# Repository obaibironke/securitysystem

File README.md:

# securitysystem
A custom motion sensor triggered security system that alerts me whenever someone enters my room. I made it because my sister kept entering myroom without me knowing so now I can catch her. It detects motion using a PIR sensor that will be soldered onto the PCB directly. It then send this information to the ESP32-S3 so that it can be logged onto the Google Sheet as well as be sent as a Telegram message. The MAX7219 display is just to show how many times motion has been detected since the system was last armed.

Hardware:

Custom PCB
XIAO ESP32-S3
PIR motion sensor
Photoresistor
MAX7219 8-digit display
Active buzzer
Arm/disarm button
Power switch
Custom enclosure

Features:

WiFi connectivity with auto-reconnect
Telegram bot alerts for motion, arm/disarm, system online
Telegram bot commands
Google Sheets event logging
Night mode that auto-disarms in daylight using photoresistor
Force disarm via Telegram
High motion alert that triggers when 3+ detections in a window
Motion counter displayed on 8-digit display, capped at 99999999
Different buzzer patterns for armed, disarmed, and motion detected
Motion timeout to prevent spam detection

BOM:

Images:

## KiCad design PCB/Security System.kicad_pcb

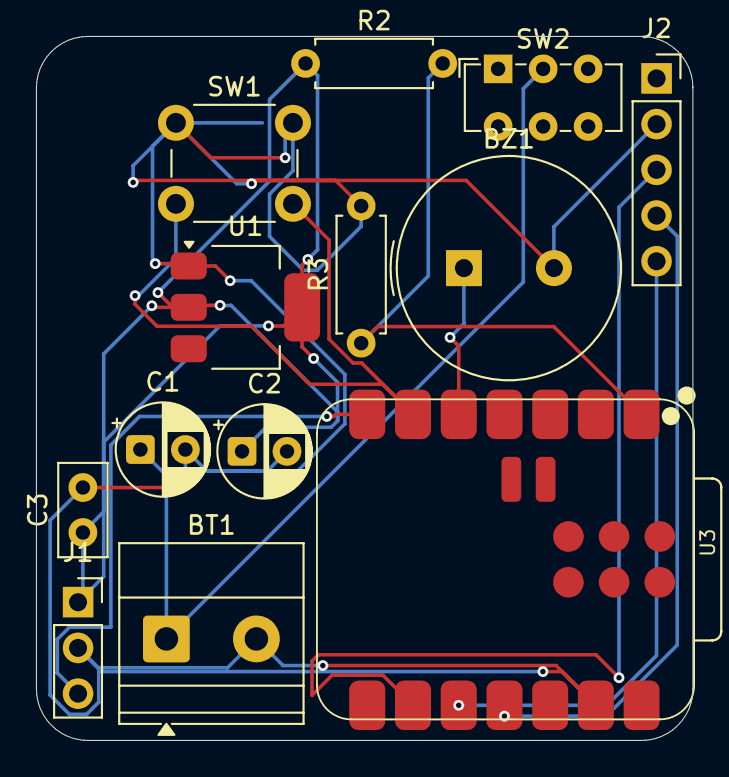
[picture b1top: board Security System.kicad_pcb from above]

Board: 2 copper layers, 36.5 x 39.1 mm, 13 parts (0 on the bottom side), 10 nets.

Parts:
BT1: Battery_Cell; TerminalBlock_Phoenix_MKDS-1,5-2_1x02_P5.00mm_Horizontal
BZ1: Buzzer; Buzzer_TDK_PS1240P02BT_D12.2mm_H6.5mm
C1, C2: C_Polarized; CP_Radial_D5.0mm_P2.50mm
C3: C; C_Disc_D5.0mm_W2.5mm_P2.50mm
J1: Conn_01x03; PinSocket_1x03_P2.54mm_Vertical
J2: Conn_01x05_Pin; PinSocket_1x05_P2.54mm_Vertical
R2: R_Photo; R_Axial_DIN0207_L6.3mm_D2.5mm_P7.62mm_Horizontal
R3: R; R_Axial_DIN0207_L6.3mm_D2.5mm_P7.62mm_Horizontal
SW1: SW_Push; SW_PUSH_6mm
SW2: SW_SPDT; SW_E-Switch_EG1271_SPDT
U1: AMS1117-3.3; SOT-223-3_TabPin2
U3: Val**; XIAO-ESP32-C3-SMD

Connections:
+3.3V: C2.1, C3.1, J1.1, R2.1, U1.2 (VO)
+BATT: BT1.1 (+), C1.1, SW2.2 (B)
GND: BT1.2 (-), BZ1.2 (-), C1.2, C2.2, C3.2, J1.2, J2.2, R3.2, SW1.1, U1.1 (GND), U3.13 (GND)
unnamed: BZ1.1 (+), U3.5 (GPIO6_D4_SDA)
unnamed: J1.3, U3.7 (GPIO21_D6_TX)
unnamed: J2.3, U3.9 (GPIO8_D8_SCK)
unnamed: J2.4, U3.11 (GPIO10_D10_MOSI)
unnamed: J2.5, U3.10 (GPIO9_D9_MISO)
unnamed: R2.2, R3.1, U3.1 (GPIO2_A0_D0)
unnamed: SW1.2, U3.6 (GPIO7_D5_SCL)

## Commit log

2026-04-09 Enhance README with hardware and features details
    Added detailed hardware and features sections to the README.
2026-04-09 Add the PCB files
2026-04-09 Add enclosure 3D models
2026-04-09 Assembled CAD Model
2026-04-09 Create 1
2026-04-09 Rename Assembled Enclosure.step to CAD/Assembled Enclosure.step
2026-04-09 Rename Security System Enclosure Base.step to CAD/Security System Enclosure Base.step
2026-04-09 Rename Security System Enclosure Top.step to CAD/Security System Enclosure Top.step
2026-04-09 Rename Security System PCB.step to CAD/Security System PCB.step
2026-04-09 Rename Security System.kicad_pcb to PCB/Security System.kicad_pcb
2026-04-09 Rename Security System.kicad_sch to PCB/Security System.kicad_sch
2026-04-09 Rename SecuritySystem.ino to Firmware/SecuritySystem.ino
2026-04-09 Enhance README with project details and images
    Expanded project description and added images.
2026-04-09 Add BOM section to README
    Added a Bill of Materials (BOM) section with components, quantities, and costs.
2026-04-25 Update README to remove BOM and add image
    Removed BOM section with component details and replaced with an image.
2026-04-29 Enhance README with detailed project features
    Expanded the project description to include logging to Google Sheets and Telegram notifications, as well as details about the MAX7219 display functionality.
